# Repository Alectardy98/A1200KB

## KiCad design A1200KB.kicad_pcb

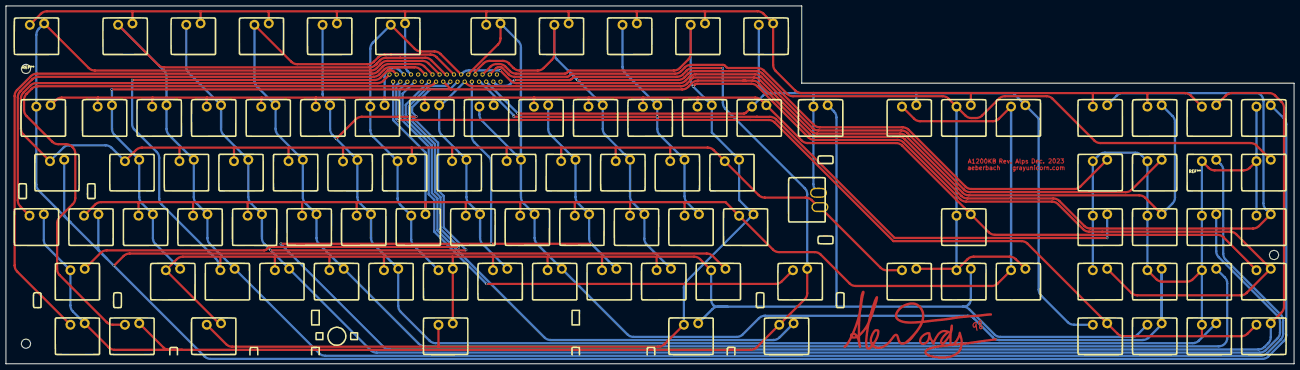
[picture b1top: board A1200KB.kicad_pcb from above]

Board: 2 copper layers, 450.0 x 125.0 mm, 102 parts (1 on the bottom side), 28 nets.

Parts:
J1: Conn_01x32_Female; FFC-1.25mm-RA-5204403245
K1: ESC; BIG_ALPS-1U
K2: F1; BIG_ALPS-1.25U
K3: F2; BIG_ALPS-1.25U
K4: F3; BIG_ALPS-1.25U
K5: F4; BIG_ALPS-1.25U
K6: F5; BIG_ALPS-1.25U
K7: F6; BIG_ALPS-1.25U
K8: F7; BIG_ALPS-1.25U
K9: F8; BIG_ALPS-1.25U
K10: F9; BIG_ALPS-1.25U
K11: F10; BIG_ALPS-1.25U
K12: TILDE; BIG_ALPS-1.25U
K13: 1; BIG_ALPS-1U
K14: 2; BIG_ALPS-1U
K15: 3; BIG_ALPS-1U
K16: 4; BIG_ALPS-1U
K17: 5; BIG_ALPS-1U
K18: 6; BIG_ALPS-1U
K19: 7; BIG_ALPS-1U
K20: 8; BIG_ALPS-1U
K21: 9; BIG_ALPS-1U
K22: 0; BIG_ALPS-1U
K23: MINUS; BIG_ALPS-1U
K24, K99: PLUS; BIG_ALPS-1U
K25: PIPE; BIG_ALPS-1U
K26: BS; BIG_ALPS-1.25U
K27, K93: DEL; BIG_ALPS-1U
K28: HELP; BIG_ALPS-1U
K29: NUM_(; BIG_ALPS-1U
K30: NUM_); BIG_ALPS-1U
K31: NUM_DIV; BIG_ALPS-1U
K32: NUM_MULT; BIG_ALPS-1U
K33: TAB; BIG_ALPS-1.75U
K34: Q; BIG_ALPS-1U
K35: W; BIG_ALPS-1U
K36: E; BIG_ALPS-1U
K37: R; BIG_ALPS-1U
K38: T; BIG_ALPS-1U
K39: Y; BIG_ALPS-1U
K40: U; BIG_ALPS-1U
K41: I; BIG_ALPS-1U
K42: O; BIG_ALPS-1U
K43: P; BIG_ALPS-1U
K44: L.CURLY; BIG_ALPS-1U
K45: R.CURLY; BIG_ALPS-1U
K46, K101: RETURN; BIG_ALPS-1U
K47: NUM_7; BIG_ALPS-1U
K48: NUM_8; BIG_ALPS-1U
K49: NUM_9; BIG_ALPS-1U
K50: NUM_MINUS; BIG_ALPS-1U
K51: CTRL; BIG_ALPS-1U
K52: CAPSLOCK; BIG_ALPS-1U
K53: A; BIG_ALPS-1U
K54: S; BIG_ALPS-1U
K55: D; BIG_ALPS-1U
K56: F; BIG_ALPS-1U
K57: G; BIG_ALPS-1U
K58: H; BIG_ALPS-1U
K59: J; BIG_ALPS-1U
K60: K; BIG_ALPS-1U
K61: L; BIG_ALPS-1U
K62: COLON; BIG_ALPS-1U
K63: "; BIG_ALPS-1U
K64: R.BLANK; BIG_ALPS-1U
K65: UP; BIG_ALPS-1U
K66: NUM_4; BIG_ALPS-1U
K67: NUM_5; BIG_ALPS-1U
K68: NUM_6; BIG_ALPS-1U
K69: NUM_PLUS; BIG_ALPS-1U
K70: L.SHIFT; BIG_ALPS-2.5U
K71: L.BLANK; BIG_ALPS-1U
K72: Z; BIG_ALPS-1U
K73: X; BIG_ALPS-1U
K74: C; BIG_ALPS-1U
K75: V; BIG_ALPS-1U
K76: B; BIG_ALPS-1U
K77: N; BIG_ALPS-1U
K78: M; BIG_ALPS-1U
K79, K100: R.CROC; BIG_ALPS-1U
K80: L.CROC; BIG_ALPS-1U
K81: QUESTION; BIG_ALPS-1U
K82: R.SHIFT; BIG_ALPS-2U
K83: LEFT; BIG_ALPS-1U
K84: DOWN; BIG_ALPS-1U
K85: RIGHT; BIG_ALPS-1U
K86: NUM_1; BIG_ALPS-1U
K87: NUM_2; BIG_ALPS-1U
K88: NUM_3; BIG_ALPS-1U
K89: NUM_ENTER; BIG_ALPS-1U
K90: L.ALT; BIG_ALPS-1U
K91: L.AMIGA; BIG_ALPS-1U
K92: SPACE; BIG_ALPS-2U
K94: R.ALT; BIG_ALPS-1U
K95: NUM_0; BIG_ALPS-1U
K96: NUM_DECIMAL; BIG_ALPS-1U
K97: SPACE; Big_ALPS-6.5U
K98: SPACE; BIG_ALPS-2.5U

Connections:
/1: J1.1, K33.1 (COL), K34.2 (ROW), K35.2 (ROW), K36.2 (ROW), K37.2 (ROW), K38.2 (ROW), K39.1 (COL), K40.2 (ROW), K41.2 (ROW), K42.2 (ROW), K43.2 (ROW), K44.2 (ROW), K45.2 (ROW), K46.1 (COL), K83.2 (ROW), K101.1 (COL)
/2: J1.2, K27.2 (ROW), K52.2 (ROW), K53.2 (ROW), K54.2 (ROW), K55.2 (ROW), K56.2 (ROW), K57.2 (ROW), K58.1 (COL), K59.2 (ROW), K60.2 (ROW), K61.2 (ROW), K62.2 (ROW), K63.2 (ROW), K64.2 (ROW), K85.2 (ROW), K93.2 (ROW)
/3: J1.3, K26.2 (ROW), K71.2 (ROW), K72.2 (ROW), K73.2 (ROW), K74.2 (ROW), K75.2 (ROW), K76.2 (ROW), K77.1 (COL), K78.2 (ROW), K79.2 (ROW), K80.2 (ROW), K81.2 (ROW), K84.1 (COL), K92.2 (ROW), K97.2 (ROW), K98.2 (ROW), K100.2 (ROW)
/4: J1.4, K32.2 (ROW), K47.2 (ROW), K48.2 (ROW), K49.2 (ROW), K50.2 (ROW), K66.2 (ROW), K67.2 (ROW), K68.2 (ROW), K69.2 (ROW), K86.2 (ROW), K87.2 (ROW), K88.2 (ROW), K89.2 (ROW), K95.1 (COL), K96.2 (ROW)
/5: J1.5, K12.2 (ROW), K13.2 (ROW), K14.2 (ROW), K15.2 (ROW), K16.2 (ROW), K17.2 (ROW), K18.1 (COL), K19.2 (ROW), K20.1 (COL), K21.2 (ROW), K22.2 (ROW), K23.2 (ROW), K24.2 (ROW), K25.1 (COL), K65.1 (COL), K99.2 (ROW)
/6: J1.6, K82.1 (COL)
/7: J1.7, K1.2 (ROW), K2.2 (ROW), K3.2 (ROW), K4.2 (ROW), K5.2 (ROW), K6.2 (ROW), K7.1 (COL), K8.2 (ROW), K9.2 (ROW), K10.2 (ROW), K11.2 (ROW), K28.2 (ROW), K29.2 (ROW), K30.2 (ROW), K31.2 (ROW)
/8: J1.8, K94.1 (COL)
/11: J1.11, K51.2 (ROW)
/12: J1.12, K70.2 (ROW)
/13: J1.13, K90.2 (ROW)
/14: J1.14, K91.2 (ROW)
/15: J1.15, K1.1 (COL), K12.1 (COL), K32.1 (COL), K33.2 (ROW), K52.1 (COL), K71.1 (COL)
/16: J1.16, K13.1 (COL), K29.1 (COL), K34.1 (COL), K53.1 (COL), K69.1 (COL), K72.1 (COL)
/17: J1.17, K2.1 (COL), K14.1 (COL), K35.1 (COL), K49.1 (COL), K54.1 (COL), K73.1 (COL)
/18: J1.18, K3.1 (COL), K15.1 (COL), K36.1 (COL), K55.1 (COL), K68.1 (COL), K74.1 (COL)
/19: J1.19, K4.1 (COL), K16.1 (COL), K37.1 (COL), K56.1 (COL), K75.1 (COL), K88.1 (COL)
/20: J1.20, K5.1 (COL), K17.1 (COL), K38.1 (COL), K57.1 (COL), K76.1 (COL), K96.1 (COL)
/21: J1.21, K6.1 (COL), K18.2 (ROW), K39.2 (ROW), K48.1 (COL), K58.2 (ROW), K77.2 (ROW)
/22: J1.22, K19.1 (COL), K30.1 (COL), K40.1 (COL), K59.1 (COL), K67.1 (COL), K78.1 (COL)
/23: J1.23, K7.2 (ROW), K20.2 (ROW), K41.1 (COL), K60.1 (COL), K79.1 (COL), K87.1 (COL), K100.1 (COL)
/24: J1.24, K21.1 (COL), K31.1 (COL), K42.1 (COL), K61.1 (COL), K80.1 (COL), K89.1 (COL)
/25: J1.25, K8.1 (COL), K22.1 (COL), K43.1 (COL), K47.1 (COL), K62.1 (COL), K81.1 (COL)
/26: J1.26, K9.1 (COL), K23.1 (COL), K44.1 (COL), K63.1 (COL), K66.1 (COL)
/27: J1.27, K10.1 (COL), K24.1 (COL), K45.1 (COL), K64.1 (COL), K86.1 (COL), K92.1 (COL), K97.1 (COL), K98.1 (COL), K99.1 (COL)
/28: J1.28, K11.1 (COL), K25.2 (ROW), K26.1 (COL), K27.1 (COL), K46.2 (ROW), K93.1 (COL), K95.2 (ROW), K101.2 (ROW)
/29: J1.29, K28.1 (COL), K50.1 (COL), K65.2 (ROW), K83.1 (COL), K84.2 (ROW), K85.1 (COL)
/30: J1.30, K51.1 (COL), K70.1 (COL), K82.2 (ROW), K90.1 (COL), K91.1 (COL), K94.2 (ROW)

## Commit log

2023-12-05 Alps
    Alps
2024-04-18 push
